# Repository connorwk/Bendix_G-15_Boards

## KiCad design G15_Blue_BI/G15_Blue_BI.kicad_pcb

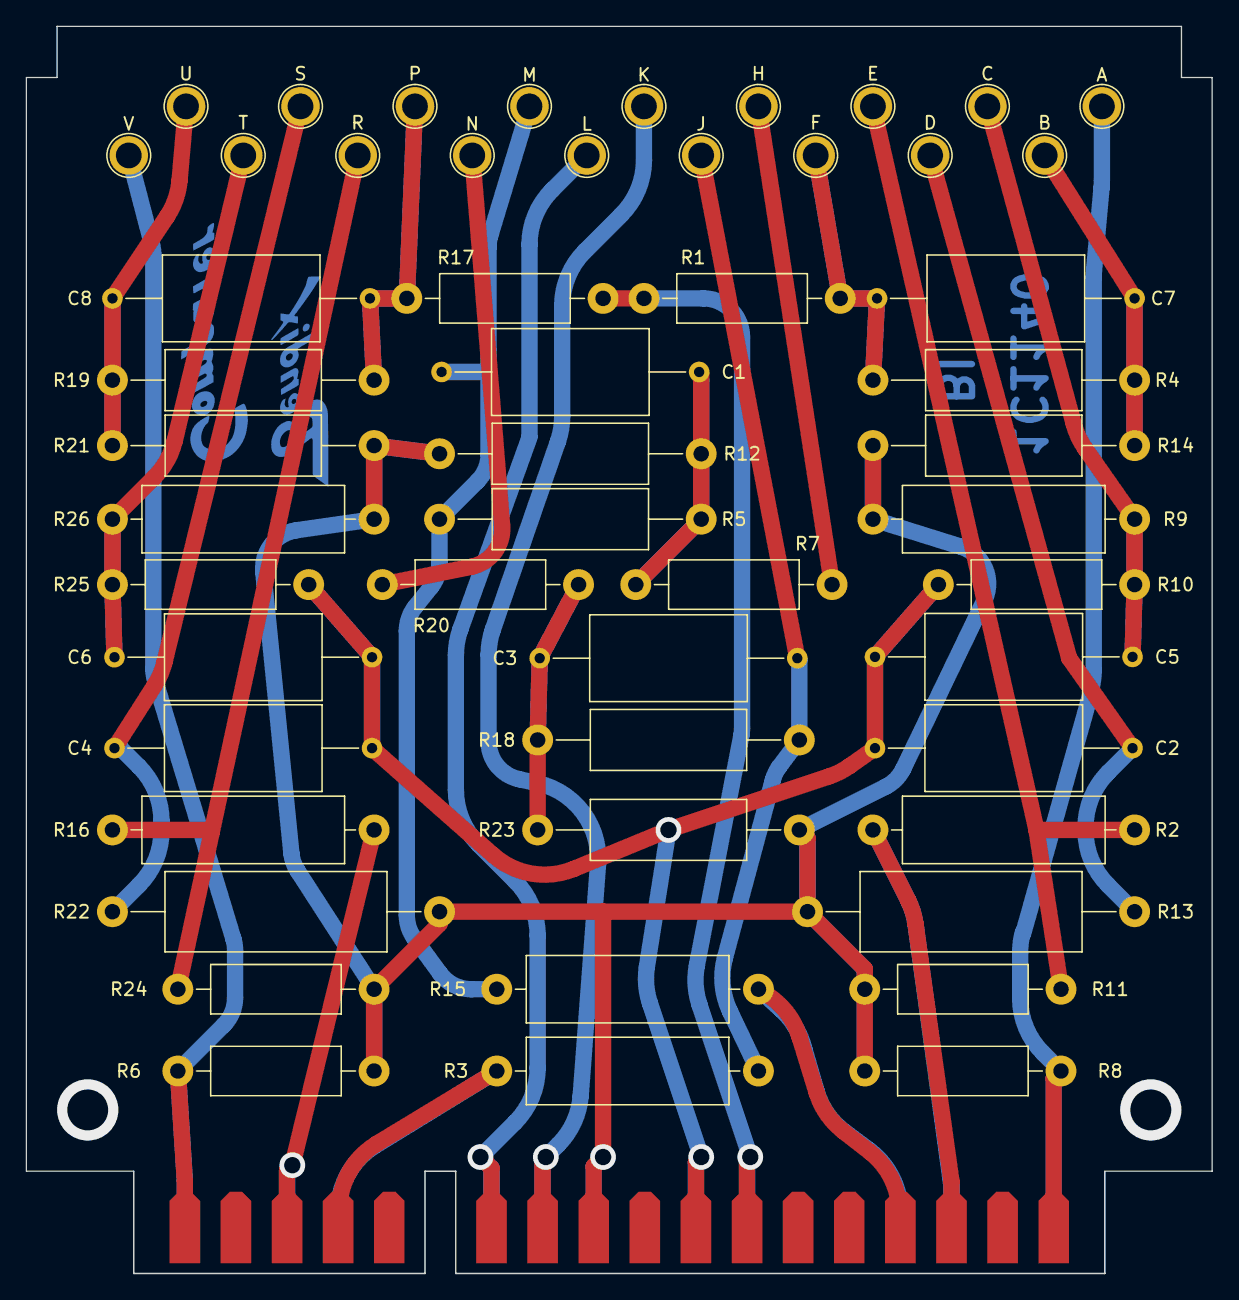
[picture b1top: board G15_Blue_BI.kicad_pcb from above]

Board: 2 copper layers, 92.1 x 96.8 mm, 53 parts (0 on the bottom side), 27 nets.

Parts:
C1, C3, C7, C8: 30nF 500V; C_Axial_L12.0mm_D6.5mm_P20.00mm_Horizontal
C2, C4, C5, C6: 300nF 500V; C_Axial_L12.0mm_D6.5mm_P20.00mm_Horizontal
J1: Conn_02x18_Row_Letter_First; Card_Edge_P_Key
R1, R17: 33K 1/2W 5%; R_Axial_DIN0411_L9.9mm_D3.6mm_P15.24mm_Horizontal
R2, R3, R15, R16: 3.9K 1W 5%; R_Axial_DIN0516_L15.5mm_D5.0mm_P20.32mm_Horizontal
R4, R19: 270K 1/4W 1%; R_Axial_DIN0414_L11.9mm_D4.5mm_P20.32mm_Horizontal
R5, R18: 82K 1/4W 1%; R_Axial_DIN0414_L11.9mm_D4.5mm_P20.32mm_Horizontal
R6, R8: 560K 1/2W 5%; R_Axial_DIN0411_L9.9mm_D3.6mm_P15.24mm_Horizontal
R7, R20: 1.2K 1/2W 5%; R_Axial_DIN0411_L9.9mm_D3.6mm_P15.24mm_Horizontal
R9, R26: 82K 1W 5%; R_Axial_DIN0516_L15.5mm_D5.0mm_P20.32mm_Horizontal
R10, R25: 4.3K 1/2W 5%; R_Axial_DIN0411_L9.9mm_D3.6mm_P15.24mm_Horizontal
R11, R24: 110K 1/2W 5%; R_Axial_DIN0411_L9.9mm_D3.6mm_P15.24mm_Horizontal
R12, R23: 33K 1/4W 1%; R_Axial_DIN0414_L11.9mm_D4.5mm_P20.32mm_Horizontal
R13, R22: 3.9K 1/2W 1%; R_Axial_DIN0617_L17.0mm_D6.0mm_P25.40mm_Horizontal
R14, R21: 56K 1/4W 1%; R_Axial_DIN0414_L11.9mm_D4.5mm_P20.32mm_Horizontal
TP1: V; TestPoint_Plated_Hole_D2.0mm
TP2: U; TestPoint_Plated_Hole_D2.0mm
TP3: T; TestPoint_Plated_Hole_D2.0mm
TP4: S; TestPoint_Plated_Hole_D2.0mm
TP5: R; TestPoint_Plated_Hole_D2.0mm
TP6: P; TestPoint_Plated_Hole_D2.0mm
TP7: N; TestPoint_Plated_Hole_D2.0mm
TP8: M; TestPoint_Plated_Hole_D2.0mm
TP9: L; TestPoint_Plated_Hole_D2.0mm
TP10: K; TestPoint_Plated_Hole_D2.0mm
TP11: J; TestPoint_Plated_Hole_D2.0mm
TP12: H; TestPoint_Plated_Hole_D2.0mm
TP13: F; TestPoint_Plated_Hole_D2.0mm
TP14: E; TestPoint_Plated_Hole_D2.0mm
TP15: D; TestPoint_Plated_Hole_D2.0mm
TP16: C; TestPoint_Plated_Hole_D2.0mm
TP17: B; TestPoint_Plated_Hole_D2.0mm
TP18: A; TestPoint_Plated_Hole_D2.0mm

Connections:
/+100V: J1.a7, J1.b7, R1.1, R17.1
/-160V: J1.a10, J1.b10, R6.2, R8.2, R9.2, R11.2, R12.2, R13.2, R14.1, R21.2, R22.2, R23.2, R24.2, R26.1
/Filament 1: J1.a11, J1.b11, TP10.1
/Filament 2: J1.a12, J1.b12, TP9.1
/Input 1: J1.a1, J1.b1, R8.1, TP18.1
/Input 2: J1.a18, J1.b18, R6.1, TP1.1
/Output 1_{0}: J1.a3, J1.b3, R2.1
/Output 1_{1}: J1.a4, J1.b4, R3.1
/Output 2_{0}: J1.a16, J1.b16, R16.1
/Output 2_{1}: J1.a15, J1.b15, R15.1
/V1P1: R16.2, R24.1, TP5.1
/V1P2: R20.2, TP7.1
/V1P3: C4.1, R22.1, TP4.1
/V1P6: C8.1, R17.2, R19.1, TP6.1
/V1P8: C6.1, R25.1, R26.2, TP3.1
/V2P1: C1.1, R3.2, R5.2, TP8.1
/V2P2: C7.2, R4.1, R14.2, TP17.1
/V2P3: C2.1, R13.1, TP15.1
/V2P6: C3.1, R15.2, R18.2, TP11.1
/V2P7: C8.2, R19.2, R21.1, TP2.1
/V3P1: C7.1, R1.2, R4.2, TP13.1
/V3P3: C5.1, R9.1, R10.1, TP16.1
/V3P6: R2.2, R11.1, TP14.1
/V3P7: R7.2, TP12.1
GND: C2.2, C4.2, C5.2, C6.2, J1.a8, J1.b8, R10.2, R25.2
unnamed: C1.2, R5.1, R7.1, R12.1
unnamed: C3.2, R18.1, R20.1, R23.1

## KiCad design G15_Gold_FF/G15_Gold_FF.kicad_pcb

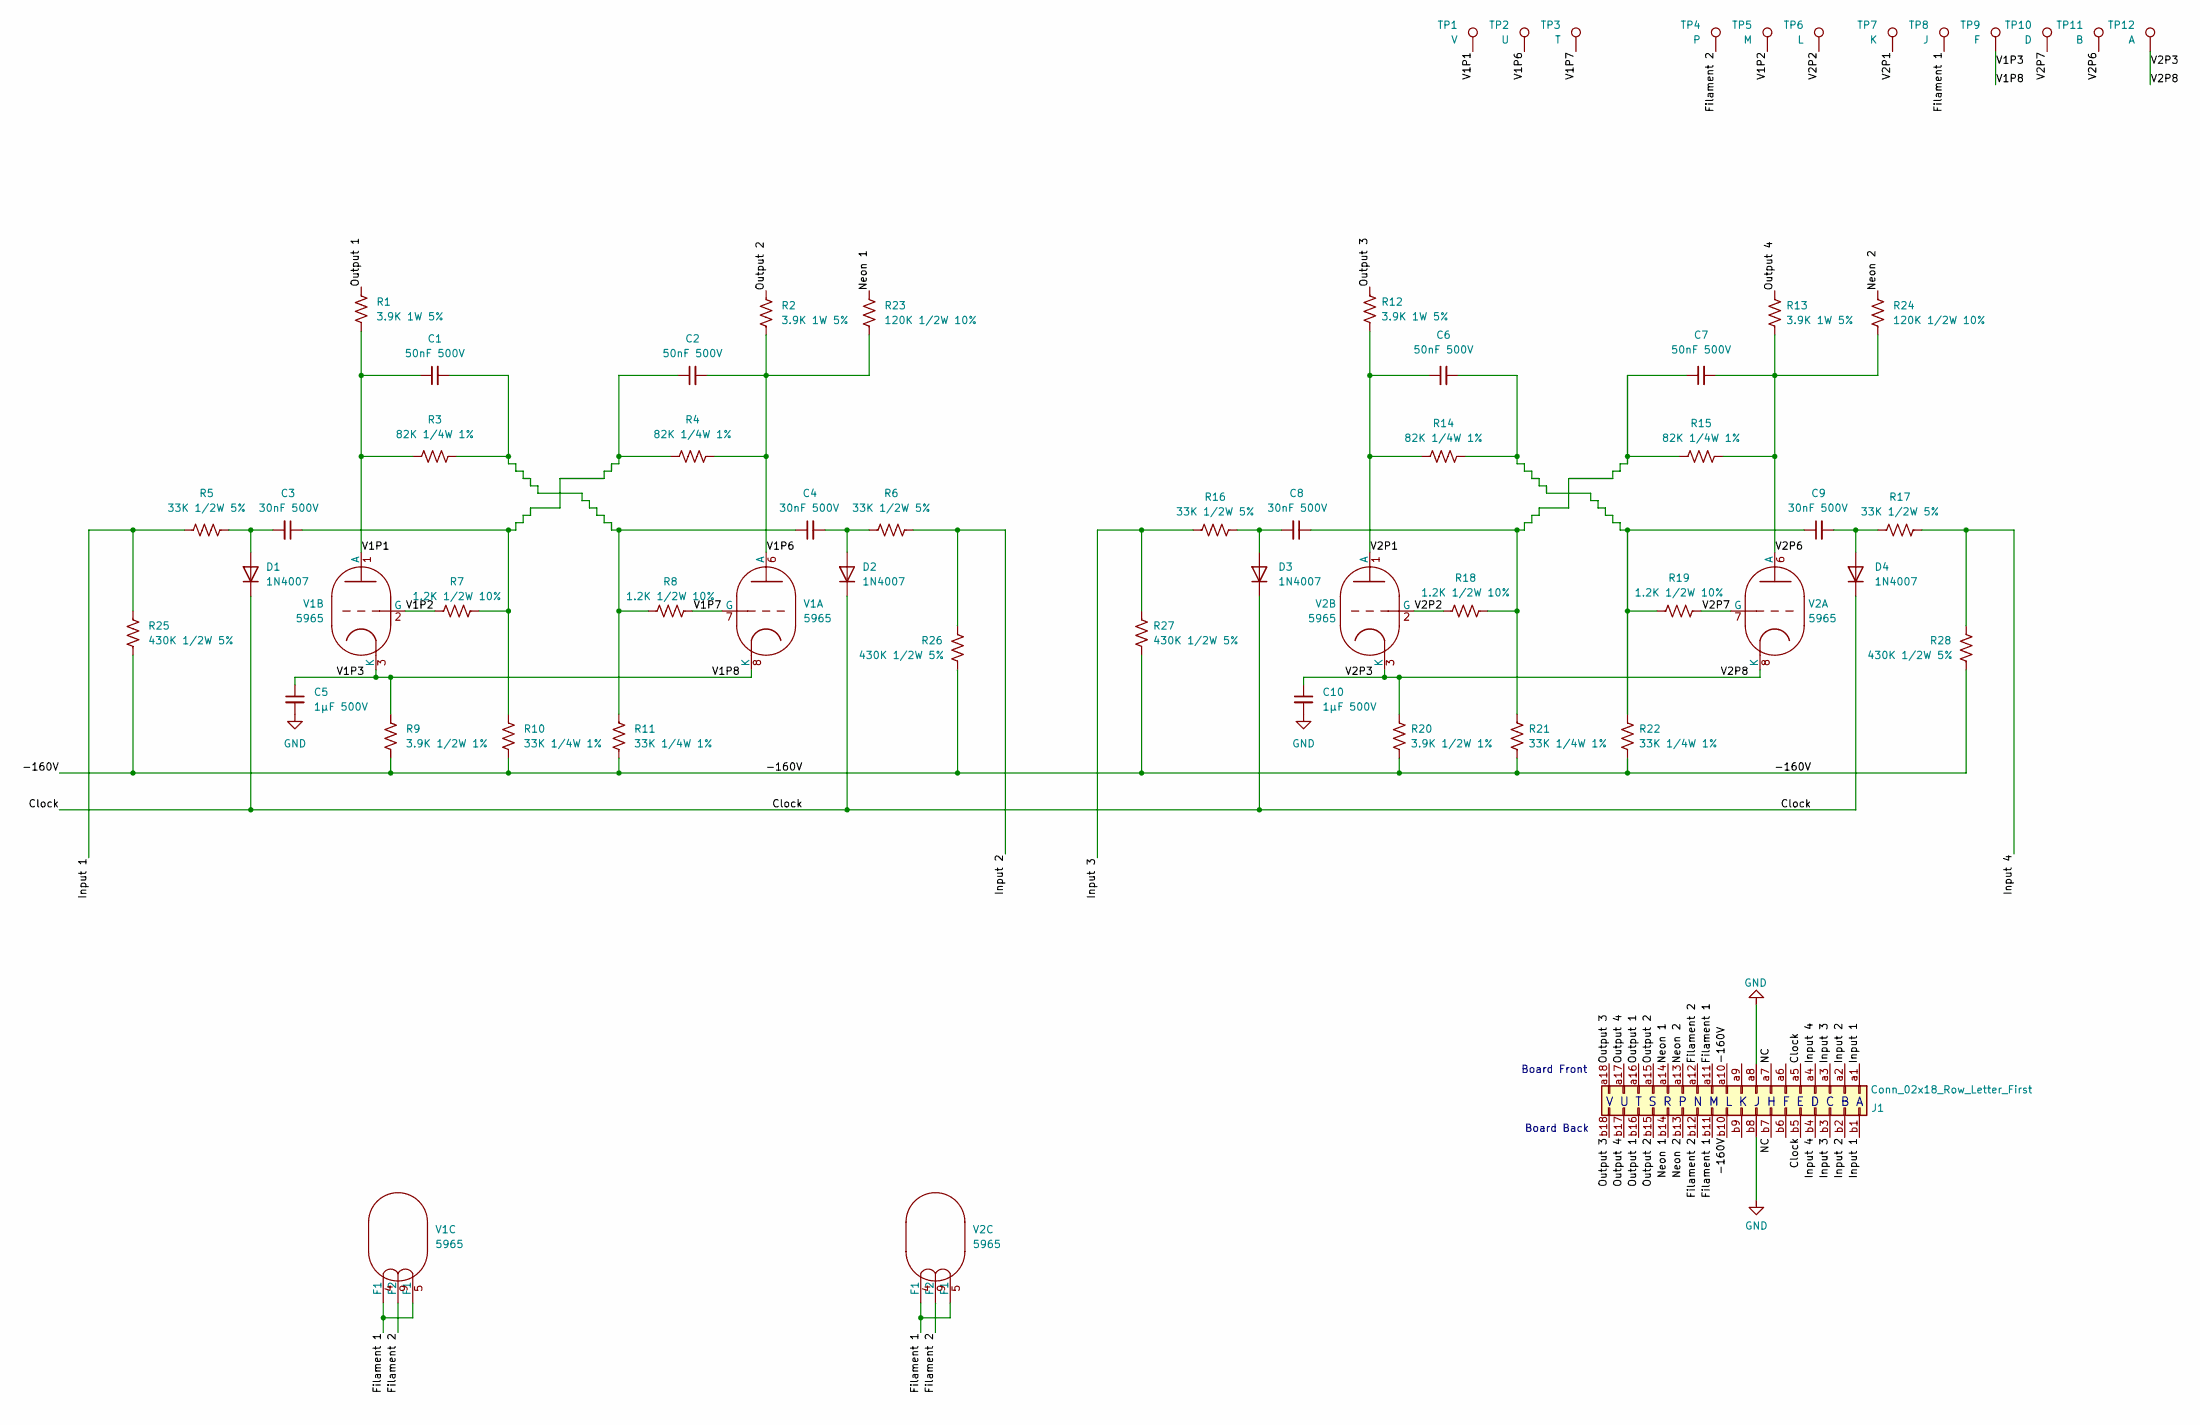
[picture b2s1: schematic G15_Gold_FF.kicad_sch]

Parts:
C1, C2, C6, C7: 50nF 500V; C_Axial_L5.1mm_D3.1mm_P15.00mm_Horizontal
C3, C4, C8, C9: 30nF 500V; C_Axial_L5.1mm_D3.1mm_P15.00mm_Horizontal
C5, C10: 1µF 500V; C_Axial_L5.1mm_D3.1mm_P15.00mm_Horizontal
D1, D2, D3, D4: 1N4007; D_DO-41_SOD81_P12.70mm_Horizontal
J1: Conn_02x18_Row_Letter_First; Card_Edge_H_Key
R1, R2, R12, R13: 3.9K 1W 5%; R_Axial_DIN0309_L9.0mm_D3.2mm_P15.24mm_Horizontal
R3, R4, R14, R15: 82K 1/4W 1%; R_Axial_DIN0309_L9.0mm_D3.2mm_P15.24mm_Horizontal
R5, R6, R16, R17: 33K 1/2W 5%; R_Axial_DIN0309_L9.0mm_D3.2mm_P15.24mm_Horizontal
R7, R8, R18, R19: 1.2K 1/2W 10%; R_Axial_DIN0309_L9.0mm_D3.2mm_P12.70mm_Horizontal
R9, R20: 3.9K 1/2W 1%; R_Axial_DIN0309_L9.0mm_D3.2mm_P15.24mm_Horizontal
R10, R11, R21, R22: 33K 1/4W 1%; R_Axial_DIN0309_L9.0mm_D3.2mm_P15.24mm_Horizontal
R23, R24: 120K 1/2W 10%; R_Axial_DIN0309_L9.0mm_D3.2mm_P15.24mm_Horizontal
R25, R26, R27, R28: 430K 1/2W 5%; R_Axial_DIN0309_L9.0mm_D3.2mm_P15.24mm_Horizontal
TP1: V; TestPoint_Plated_Hole_D2.0mm
TP2: U; TestPoint_Plated_Hole_D2.0mm
TP3: T; TestPoint_Plated_Hole_D2.0mm
TP4: P; TestPoint_Plated_Hole_D2.0mm
TP5: M; TestPoint_Plated_Hole_D2.0mm
TP6: L; TestPoint_Plated_Hole_D2.0mm
TP7: K; TestPoint_Plated_Hole_D2.0mm
TP8: J; TestPoint_Plated_Hole_D2.0mm
TP9: F; TestPoint_Plated_Hole_D2.0mm
TP10: D; TestPoint_Plated_Hole_D2.0mm
TP11: B; TestPoint_Plated_Hole_D2.0mm
TP12: A; TestPoint_Plated_Hole_D2.0mm
V1, V2: 5965

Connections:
/-160V: J1.a10, J1.b10, R9.2, R10.1, R11.2, R20.2, R21.1, R22.2, R25.2, R26.2, R27.2, R28.2
/Clock: D1.1 (K), D2.1 (K), D3.1 (K), D4.1 (K), J1.a5, J1.b5
/Filament 1: J1.a11, J1.b11, TP8.1, V1.4 (F1), V1.5 (F1), V2.4 (F1), V2.5 (F1)
/Filament 2: J1.a12, J1.b12, TP4.1, V1.9 (F2), V2.9 (F2)
/Input 1: J1.a1, J1.b1, R5.1, R25.1
/Input 2: J1.a2, J1.b2, R6.1, R26.1
/Input 3: J1.a3, J1.b3, R16.1, R27.1
/Input 4: J1.a4, J1.b4, R17.1, R28.1
/Neon 1: J1.a14, J1.b14, R23.1
/Neon 2: J1.a13, J1.b13, R24.1
/Output 1: J1.a16, J1.b16, R1.1
/Output 2: J1.a15, J1.b15, R2.1
/Output 3: J1.a18, J1.b18, R12.1
/Output 4: J1.a17, J1.b17, R13.1
/V1P1: C1.1, R1.2, R3.2, TP1.1, V1.1 (A)
/V1P2: R7.2, TP5.1, V1.2 (G)
/V1P3: C5.1, R9.1, TP9.1, V1.3 (K), V1.8 (K)
/V1P6: C2.2, R2.2, R4.1, R23.2, TP2.1, V1.6 (A)
/V1P7: R8.1, TP3.1, V1.7 (G)
/V2P1: C6.1, R12.2, R14.2, TP7.1, V2.1 (A)
/V2P2: R18.2, TP6.1, V2.2 (G)
/V2P3: C10.1, R20.1, TP12.1, V2.3 (K), V2.8 (K)
/V2P6: C7.2, R13.2, R15.1, R24.2, TP11.1, V2.6 (A)
/V2P7: R19.1, TP10.1, V2.7 (G)
GND: C5.2, C10.2, J1.a8, J1.b8
unnamed: C1.2, C4.1, R3.1, R8.2, R11.1
unnamed: C2.1, C3.1, R4.2, R7.1, R10.2
unnamed: C3.2, D1.2 (A), R5.2
unnamed: C4.2, D2.2 (A), R6.2
unnamed: C6.2, C9.1, R14.1, R19.2, R22.1
unnamed: C7.1, C8.1, R15.2, R18.1, R21.2
unnamed: C8.2, D3.2 (A), R16.2
unnamed: C9.2, D4.2 (A), R17.2

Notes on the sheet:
Board Back
Board Front
V U T S R P N M L K J H F E D C B A

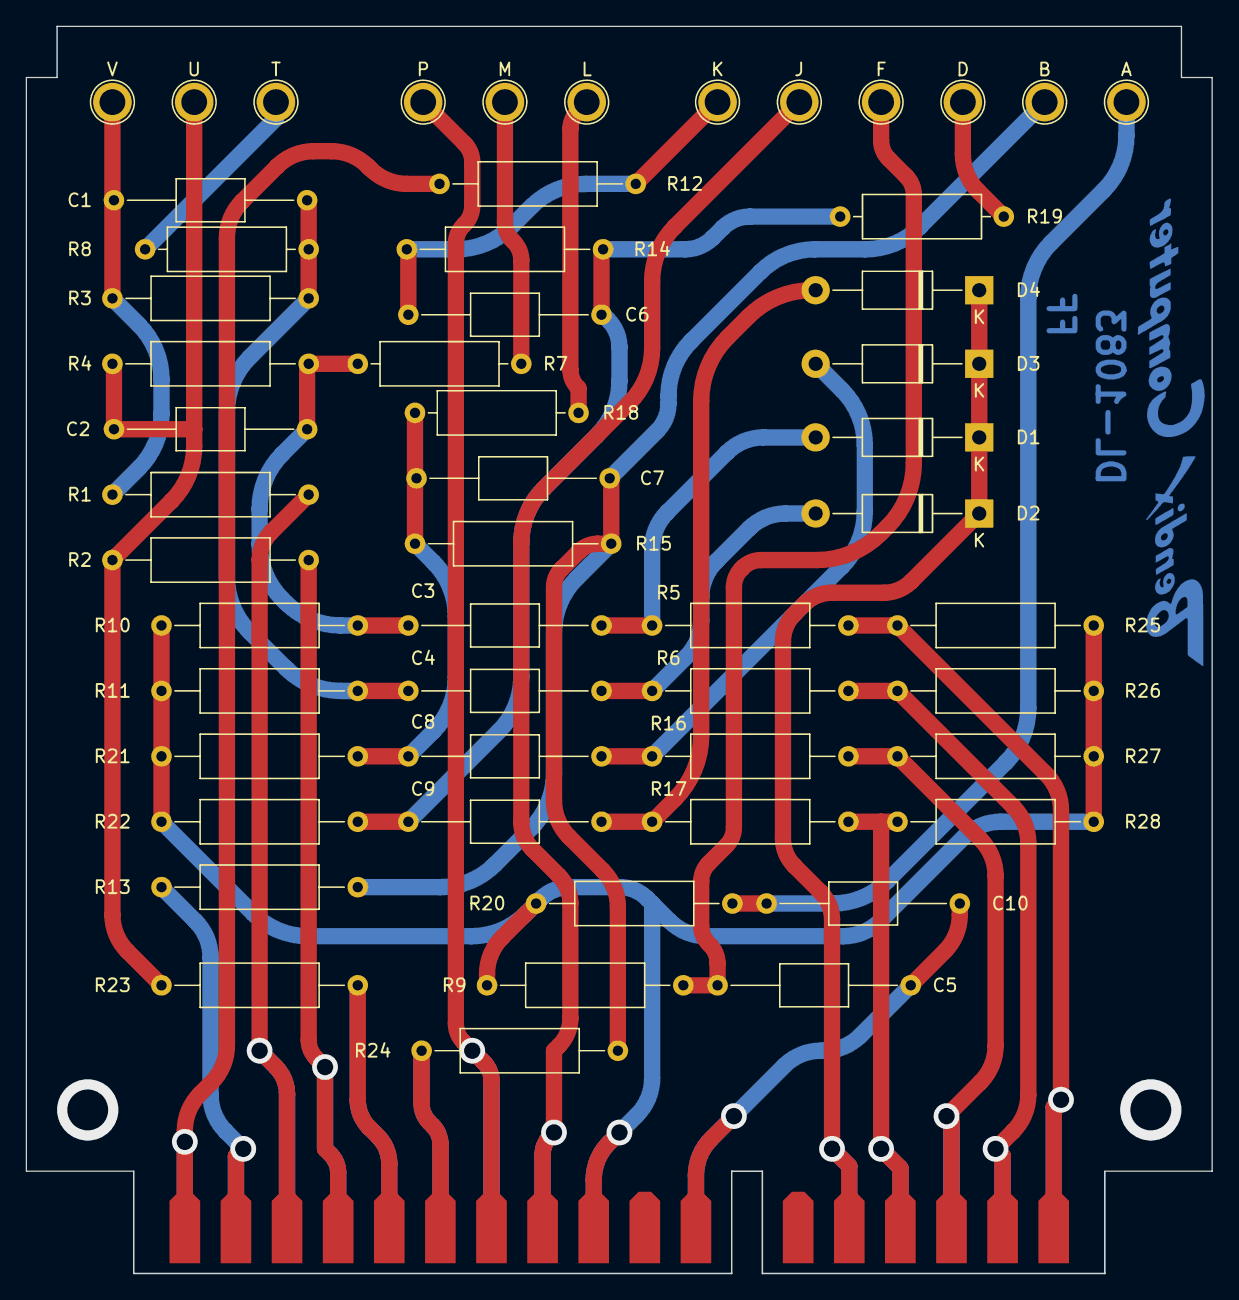
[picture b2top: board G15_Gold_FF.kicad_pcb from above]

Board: 2 copper layers, 92.1 x 96.8 mm, 55 parts (0 on the bottom side), 33 nets.

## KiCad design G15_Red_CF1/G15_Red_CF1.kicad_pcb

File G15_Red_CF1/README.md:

# Cathode Follower 1, Red Handle, For Bendix G-15 CPU
[Schematic](G15_Red_CF1_Schematic.pdf)

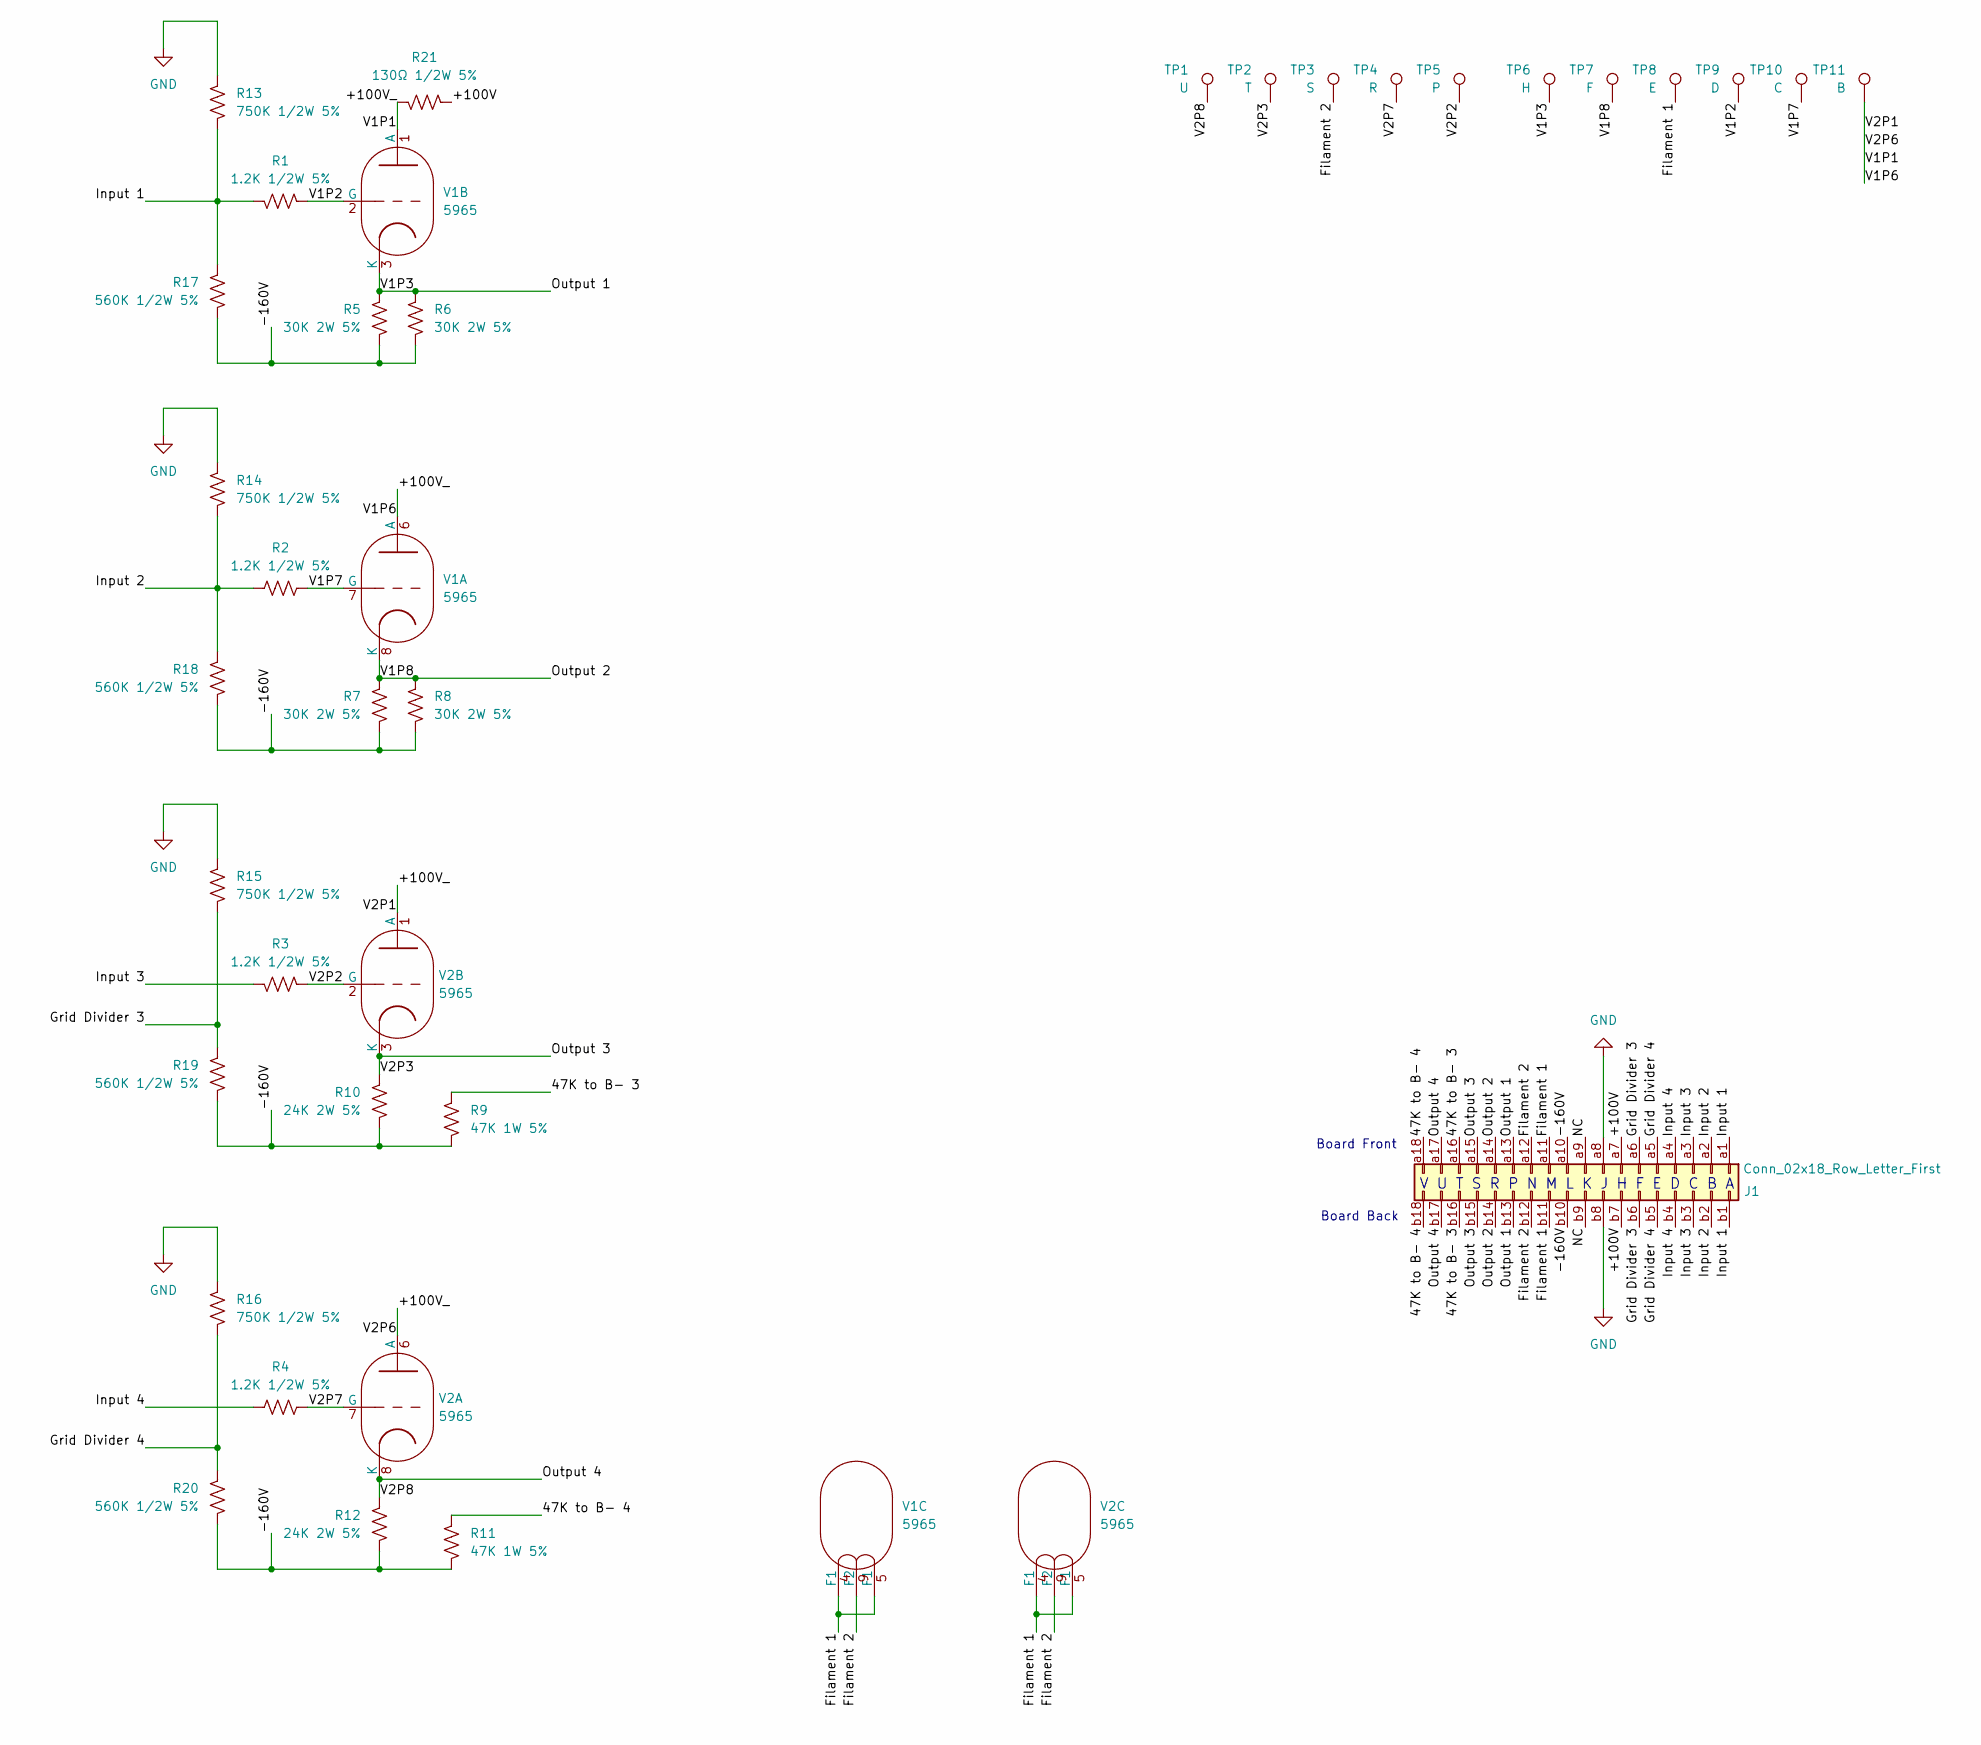
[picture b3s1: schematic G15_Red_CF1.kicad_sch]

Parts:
J1: Conn_02x18_Row_Letter_First; Card_Edge_K_Key
R1, R2, R3, R4: 1.2K 1/2W 5%; R_Axial_DIN0309_L9.0mm_D3.2mm_P15.24mm_Horizontal
R5, R6, R7, R8: 30K 2W 5%; R_Axial_DIN0617_L17.0mm_D6.0mm_P25.40mm_Horizontal
R9, R11: 47K 1W 5%; R_Axial_DIN0516_L15.5mm_D5.0mm_P20.32mm_Horizontal
R10, R12: 24K 2W 5%; R_Axial_DIN0617_L17.0mm_D6.0mm_P25.40mm_Horizontal
R13, R14, R15, R16: 750K 1/2W 5%; R_Axial_DIN0309_L9.0mm_D3.2mm_P15.24mm_Horizontal
R17, R18, R19, R20: 560K 1/2W 5%; R_Axial_DIN0309_L9.0mm_D3.2mm_P15.24mm_Horizontal
R21: 130Ω 1/2W 5%; R_Axial_DIN0309_L9.0mm_D3.2mm_P15.24mm_Horizontal
TP1: U; TestPoint_Plated_Hole_D2.0mm
TP2: T; TestPoint_Plated_Hole_D2.0mm
TP3: S; TestPoint_Plated_Hole_D2.0mm
TP4: R; TestPoint_Plated_Hole_D2.0mm
TP5: P; TestPoint_Plated_Hole_D2.0mm
TP6: H; TestPoint_Plated_Hole_D2.0mm
TP7: F; TestPoint_Plated_Hole_D2.0mm
TP8: E; TestPoint_Plated_Hole_D2.0mm
TP9: D; TestPoint_Plated_Hole_D2.0mm
TP10: C; TestPoint_Plated_Hole_D2.0mm
TP11: B; TestPoint_Plated_Hole_D2.0mm
V1, V2: 5965

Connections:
/47K to B- 3: J1.a16, J1.b16, R9.1
/47K to B- 4: J1.a18, J1.b18, R11.1
/+100V: J1.a7, J1.b7, R21.2
/+100V_: R21.1, TP11.1, V1.1 (A), V1.6 (A), V2.1 (A), V2.6 (A)
/-160V: J1.a10, J1.b10, R5.1, R6.2, R7.1, R8.2, R9.2, R10.1, R11.2, R12.1, R17.1, R18.1, R19.1, R20.1
/Filament 1: J1.a11, J1.b11, TP8.1, V1.4 (F1), V1.5 (F1), V2.4 (F1), V2.5 (F1)
/Filament 2: J1.a12, J1.b12, TP3.1, V1.9 (F2), V2.9 (F2)
/Grid Divider 3: J1.a6, J1.b6, R15.2, R19.2
/Grid Divider 4: J1.a5, J1.b5, R16.2, R20.2
/Input 1: J1.a1, J1.b1, R1.1, R13.2, R17.2
/Input 2: J1.a2, J1.b2, R2.2, R14.2, R18.2
/Input 3: J1.a3, J1.b3, R3.1
/Input 4: J1.a4, J1.b4, R4.2
/Output 1: J1.a13, J1.b13, R5.2, R6.1, TP6.1, V1.3 (K)
/Output 2: J1.a14, J1.b14, R7.2, R8.1, TP7.1, V1.8 (K)
/Output 3: J1.a15, J1.b15, R10.2, TP2.1, V2.3 (K)
/Output 4: J1.a17, J1.b17, R12.2, TP1.1, V2.8 (K)
/V1P2: R1.2, TP9.1, V1.2 (G)
/V1P7: R2.1, TP10.1, V1.7 (G)
/V2P2: R3.2, TP5.1, V2.2 (G)
/V2P7: R4.1, TP4.1, V2.7 (G)
GND: J1.a8, J1.b8, R13.1, R14.1, R15.1, R16.1

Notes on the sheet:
Board Back
Board Front
V U T S R P N M L K J H F E D C B A

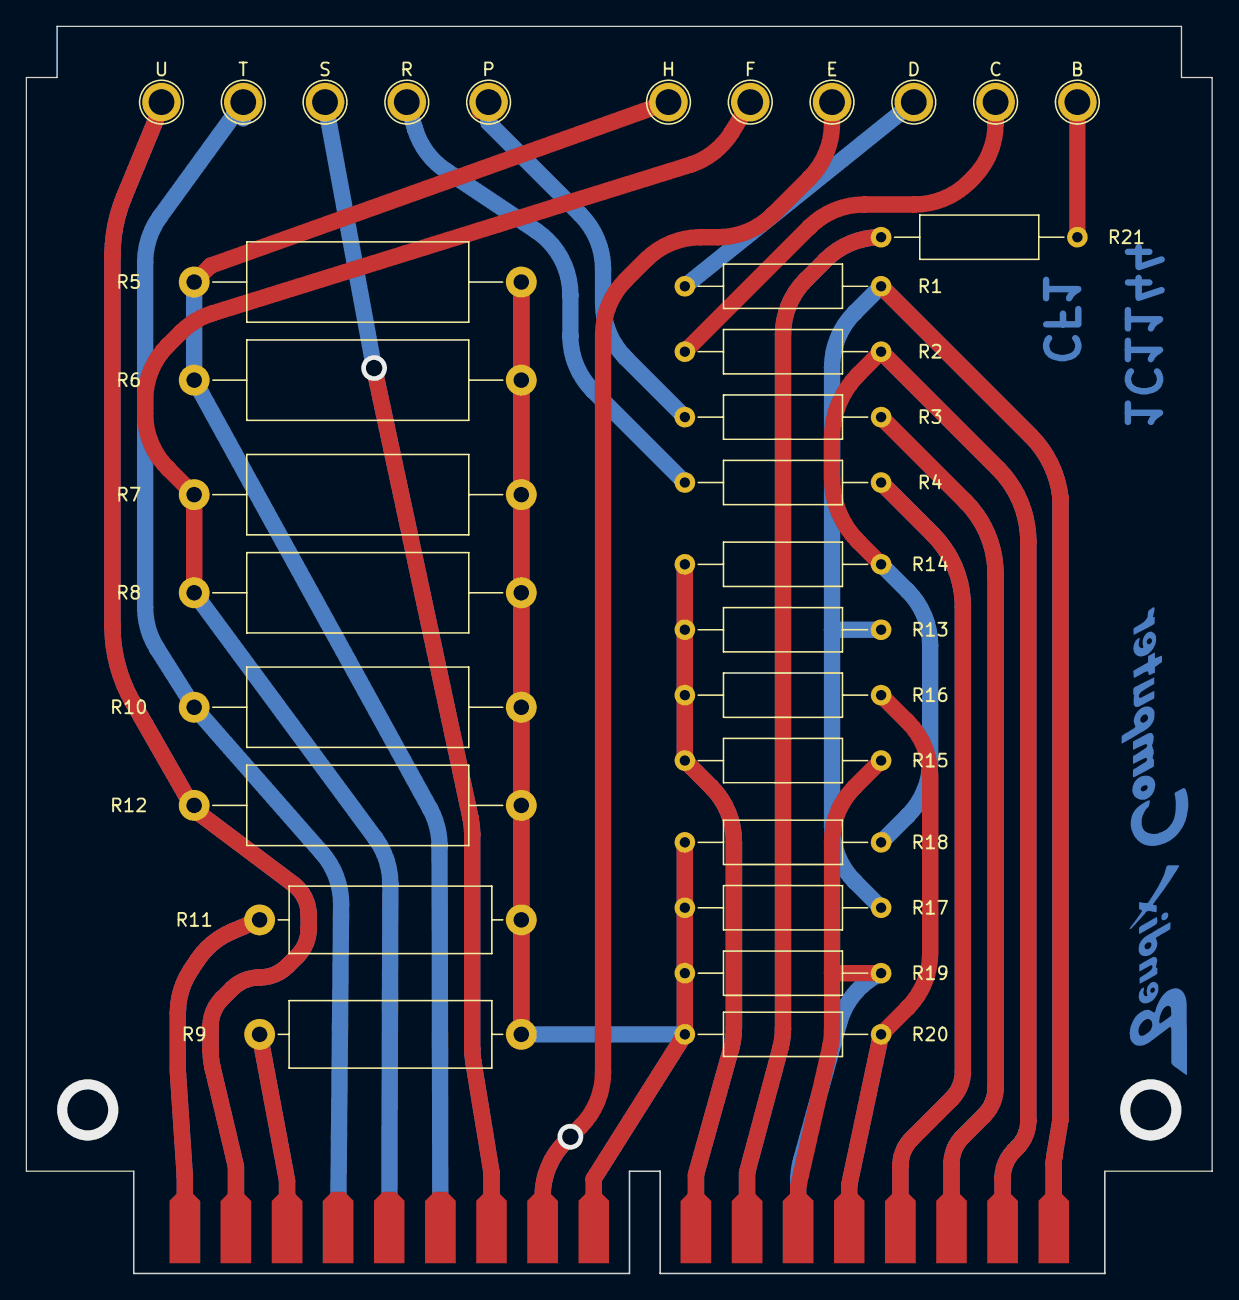
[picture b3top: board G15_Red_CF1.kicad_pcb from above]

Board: 2 copper layers, 92.1 x 96.8 mm, 33 parts (0 on the bottom side), 22 nets.
